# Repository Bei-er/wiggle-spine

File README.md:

This is the Wiggle **Spine**, an open hardware design for [Wiggleport](http://wiggleport.org)'s power and data hub.

* Each "spine" board has a 480 Mbit/s USB 2.0 uplink and 7 connectors for **modules**.
* Drive up to 14 speakers at 48/96 kHz per channel from one USB port.
* Connect sensors and lights, sync them perfectly with sound and each other.
* Use it to create objects and environments that are perfectly synchronized with immersive sound and vibration.
* Connect other audio-frequency devices like vibration transducers, LED strobes, and modular synthesizers.
* Use all the processing power in your PC, or run from an embedded Linux board like the Raspberry Pi 2.
* Gain accurate control of I/O timing from high-level languages like Javascript.

Scale it up or down
-------------------

* Multiple spines can be synchronized with cheap TOSLINK-style optical cables
  * USB links can go to the same or different computers, depending on how much processing power you need
  * Everyone shares a common audio clock and timestamps

* The spine also has a built-in DMX output so it's easy to add inexpensive lights and effects to your project
  * The output has galvanic isolation, to prevent grounding problems or audio hum
  * The DMX outputs can of course synchronize with all other inputs and outputs

* Wiggleport distributes power too, not just data
  * Flexible power input, 5 to 24 volts 
  * Lots of power, over 300 watts total
  * Each module has 5V, 3.3V, and 5-24V available
  * There's also a 5V power output for running a Raspberry Pi or other small computer
  * Also there's a watchdog timer, to reboot the computer if it stops running for any reason

Internals
---------

Wiggleport is an open source hardware design optimized for simple and straightforward real-time performance. It's based around an FTDI FT2232H high-speed USB FIFO interface, combined with a precision clock synthesizer and a tiny FPGA for glue logic. It stays simple and inexpensive by doing much of the work in software, relying on the powerful CPUs available on even small embedded Linux boards now.

Wiggleport isn't really a sound card, even though you can use it as one. It has its own APIs for C++, MIDI, and Javascript. You can write code for precisely timed multichannel sound installations on your laptop on Mac OS, for example, and run the same code on a Raspberry Pi later on.

Going even deeper, Wiggleport is really kind of a construction kit for hardware and drivers that stream signals in real-time. This reconfigurability is what lets Wiggleport automatically configure the various add-on modules, but you can also use this core directly to create your own hardware, with or without including an FPGA.

**Coming soon**... development is happening here now! You can follow the progress at [wiggleport.org](http://wiggleport.org).

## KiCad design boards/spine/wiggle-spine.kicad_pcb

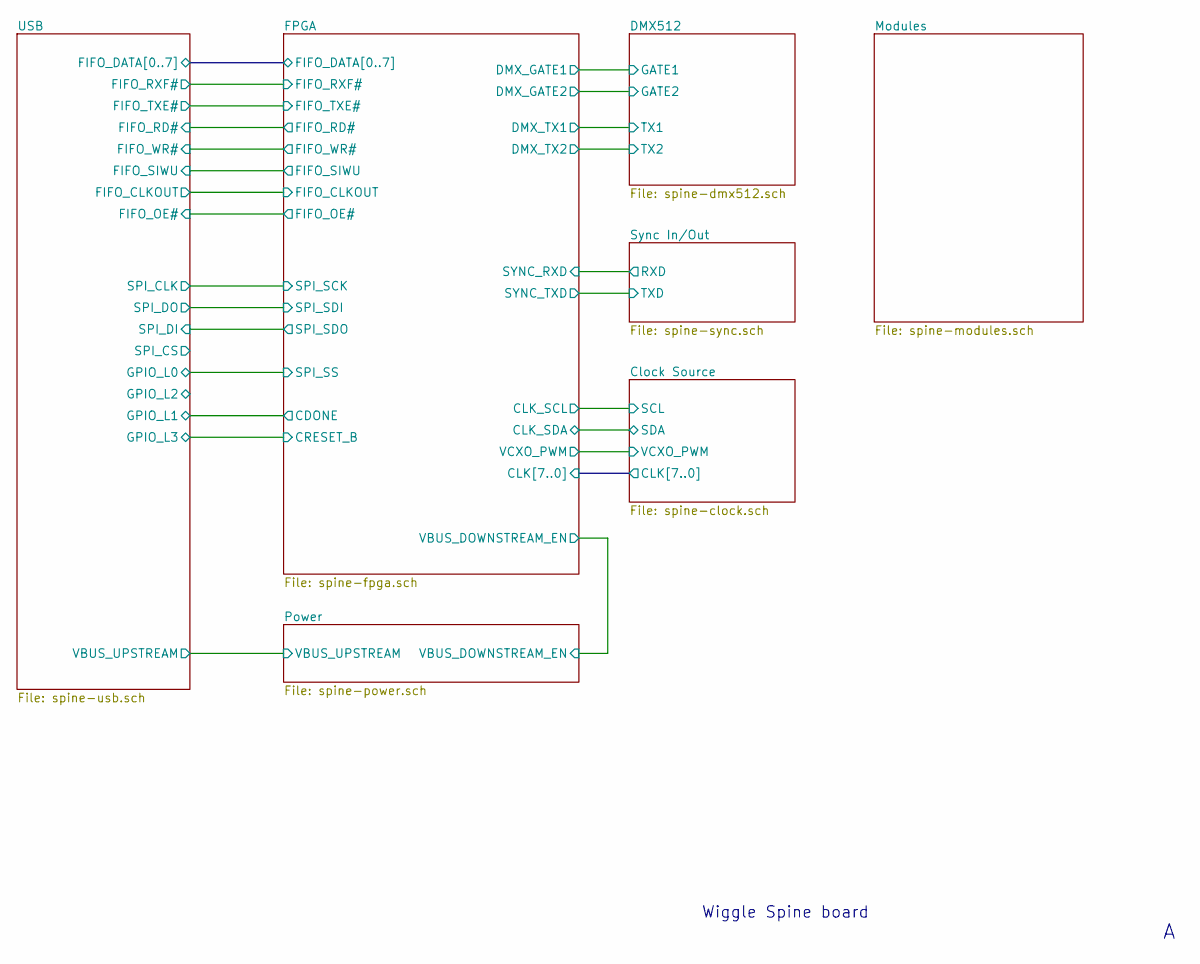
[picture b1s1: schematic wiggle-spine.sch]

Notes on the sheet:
Wiggle Spine board

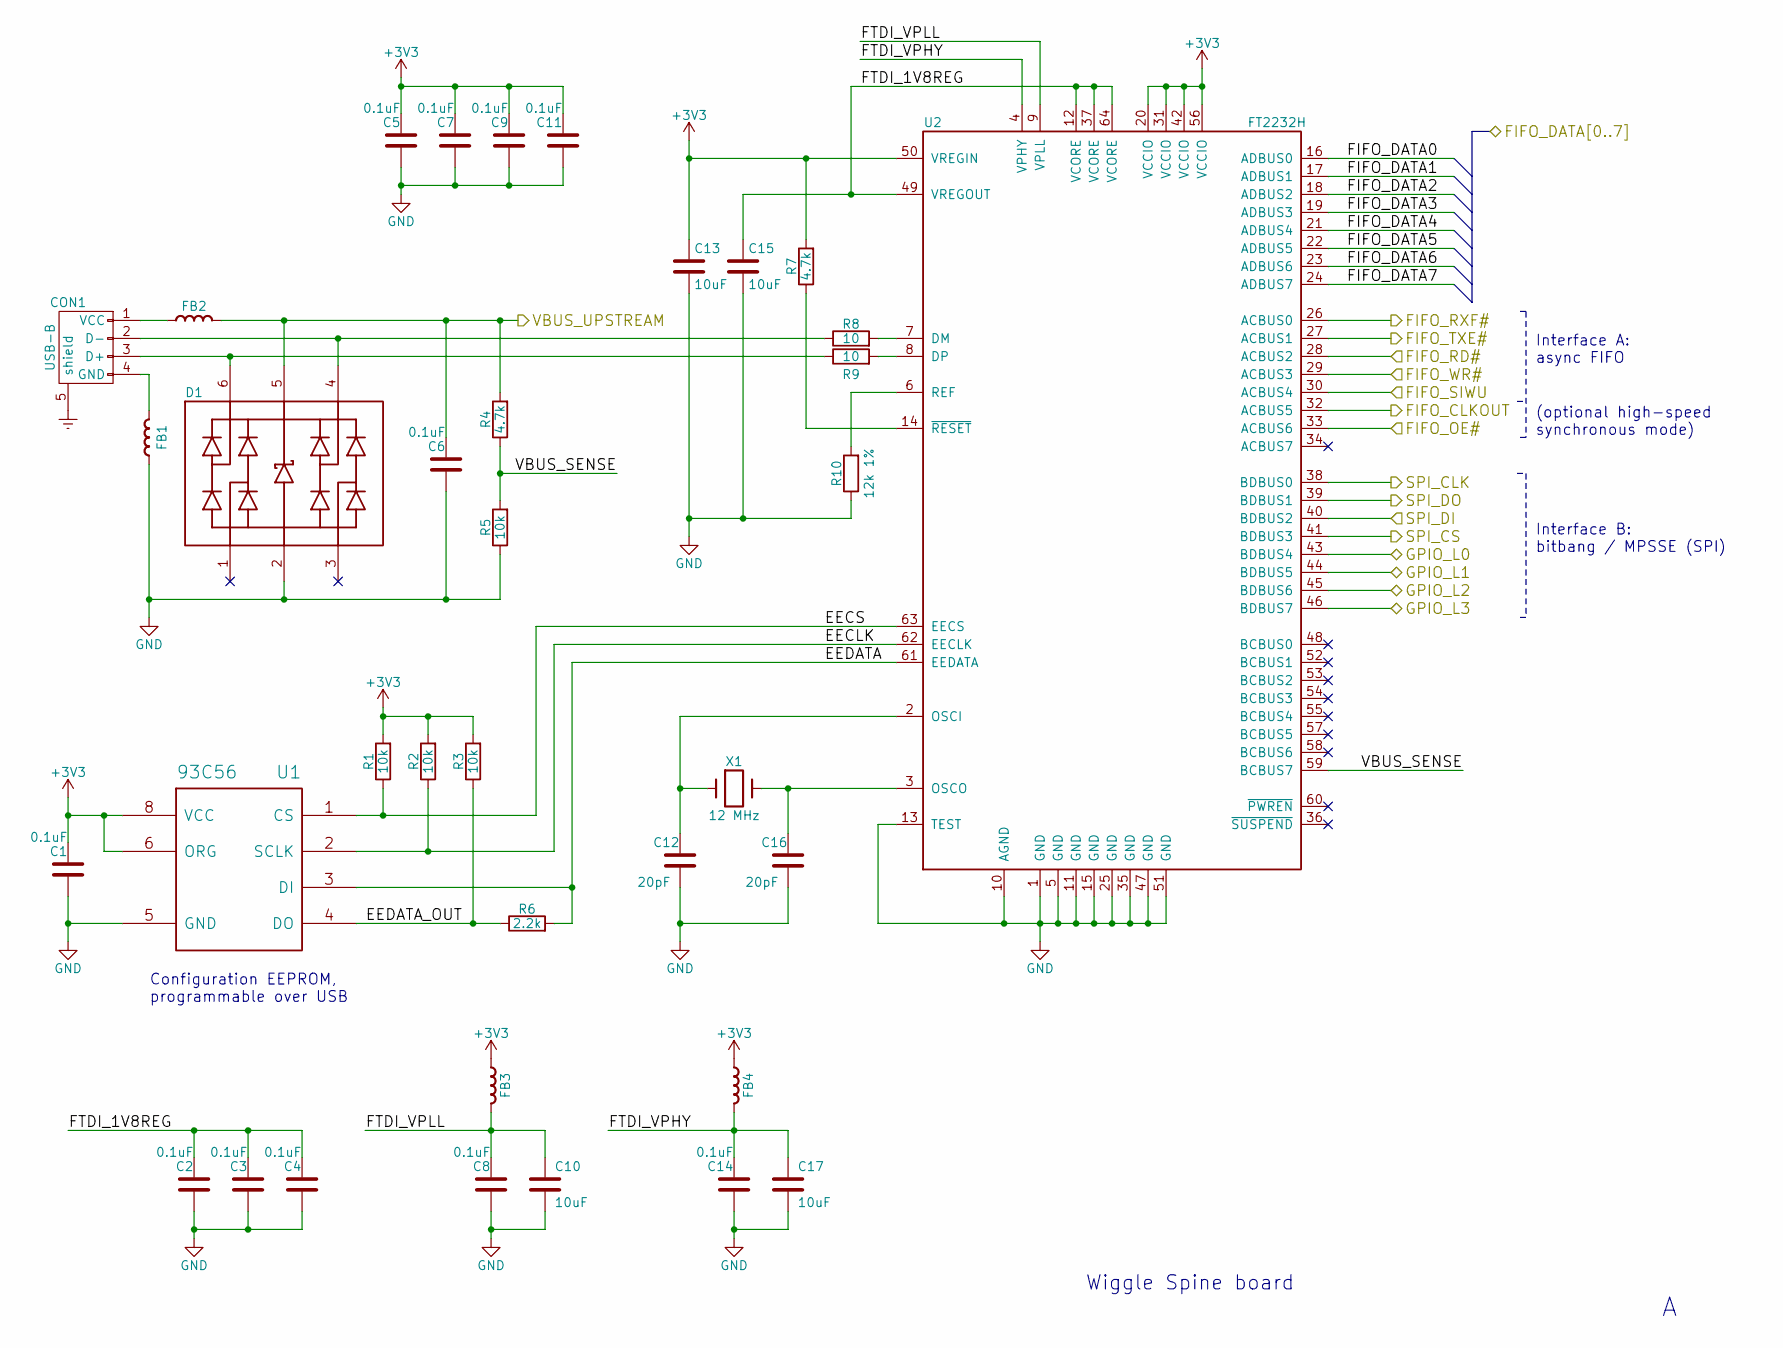
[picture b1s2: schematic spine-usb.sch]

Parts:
C1, C2, C3, C4, C5, C6, C7, C8, C9, C11, C14: 0.1uF; C_0805
C10, C13, C15, C17: 10uF; C_1206
C12, C16: 20pF; C_0805
CON1: USB-B; USB_B
D1: TVS DIODE 5.5VWM; SC-70-6
FB1, FB2, FB3, FB4: Ferrite bead; R_0805
R1, R2, R3, R5: 10k; R_0805
R4, R7: 4.7k; R_0805
R6: 2.2k; R_0805
R8, R9: 10; R_0805
R10: 12k 1%; R_0805
U1: 93C56; SOIC-8_3.9x4.9mm_Pitch1.27mm
U2: FT2232H; LQFP-64_10x10mm_Pitch0.5mm
X1: 12 MHz; Crystal_HC49-SD_SMD

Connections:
/FPGA/CDONE: U2.44 (BDBUS5); also elsewhere on the board
/FPGA/CRESET_B: U2.46 (BDBUS7); also elsewhere on the board
/FPGA/FIFO_CLKOUT: U2.32 (ACBUS5); also elsewhere on the board
/FPGA/FIFO_DATA0: U2.16 (ADBUS0); also elsewhere on the board
/FPGA/FIFO_DATA1: U2.17 (ADBUS1); also elsewhere on the board
/FPGA/FIFO_DATA2: U2.18 (ADBUS2); also elsewhere on the board
/FPGA/FIFO_DATA3: U2.19 (ADBUS3); also elsewhere on the board
/FPGA/FIFO_DATA4: U2.21 (ADBUS4); also elsewhere on the board
/FPGA/FIFO_DATA5: U2.22 (ADBUS5); also elsewhere on the board
/FPGA/FIFO_DATA6: U2.23 (ADBUS6); also elsewhere on the board
/FPGA/FIFO_DATA7: U2.24 (ADBUS7); also elsewhere on the board
/FPGA/FIFO_OE#: U2.33 (ACBUS6); also elsewhere on the board
/FPGA/FIFO_RD#: U2.28 (ACBUS2); also elsewhere on the board
/FPGA/FIFO_RXF#: U2.26 (ACBUS0); also elsewhere on the board
/FPGA/FIFO_SIWU: U2.30 (ACBUS4); also elsewhere on the board
/FPGA/FIFO_TXE#: U2.27 (ACBUS1); also elsewhere on the board
/FPGA/FIFO_WR#: U2.29 (ACBUS3); also elsewhere on the board
/Power/VBUS_UPSTREAM: C6.2, D1.5, FB2.2, R4.2; also elsewhere on the board
/USB/EECLK: R2.1, U1.2 (SCLK), U2.62 (EECLK)
/USB/EECS: R1.1, U1.1 (CS), U2.63 (EECS)
/USB/EEDATA: R6.2, U1.3 (DI), U2.61 (EEDATA)
/USB/EEDATA_OUT: R3.1, R6.1, U1.4 (DO)
/USB/FTDI_1V8REG: C2.2, C3.2, C4.2, C15.1, U2.12 (VCORE), U2.37 (VCORE), U2.49 (VREGOUT), U2.64 (VCORE)
/USB/FTDI_VPHY: C14.2, C17.1, FB4.2, U2.4 (VPHY)
/USB/FTDI_VPLL: C8.2, C10.1, FB3.2, U2.9 (VPLL)
/USB/GPIO_L0: U2.43 (BDBUS4); also elsewhere on the board
/USB/SPI_CLK: U2.38 (BDBUS0); also elsewhere on the board
/USB/SPI_DI: U2.40 (BDBUS2); also elsewhere on the board
/USB/SPI_DO: U2.39 (BDBUS1); also elsewhere on the board
/USB/VBUS_SENSE: R4.1, R5.2, U2.59 (BCBUS7)
Earth: CON1.5 (shield); also elsewhere on the board
GND: C1.1, C2.1, C3.1, C4.1, C5.1, C6.1, C7.1, C8.1, C9.1, C10.2, C11.1, C12.1, C13.2, C14.1, C15.2, C16.1, C17.2, D1.2, FB1.1, R5.1, R10.1, U1.5 (GND), U2.1 (GND), U2.5 (GND), U2.10 (AGND), U2.11 (GND), U2.13 (TEST), U2.15 (GND), U2.25 (GND), U2.35 (GND), U2.47 (GND), U2.51 (GND); also elsewhere on the board
unnamed: C12.2, U2.2 (OSCI), X1.1
unnamed: C16.2, U2.3 (OSCO), X1.2
unnamed: CON1.1 (VCC), FB2.1
unnamed: CON1.2 (D-), D1.4, R8.1
unnamed: CON1.3 (D+), D1.6, R9.1
unnamed: CON1.4 (GND), FB1.2
unnamed: R7.1, U2.14 (~RESET)
unnamed: R8.2, U2.7 (DM)
unnamed: R9.2, U2.8 (DP)
unnamed: R10.2, U2.6 (REF)

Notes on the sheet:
(optional high-speed synchronous mode)
Interface A: async FIFO
Interface B: bitbang / MPSSE (SPI)
Configuration EEPROM, programmable over USB
Wiggle Spine board

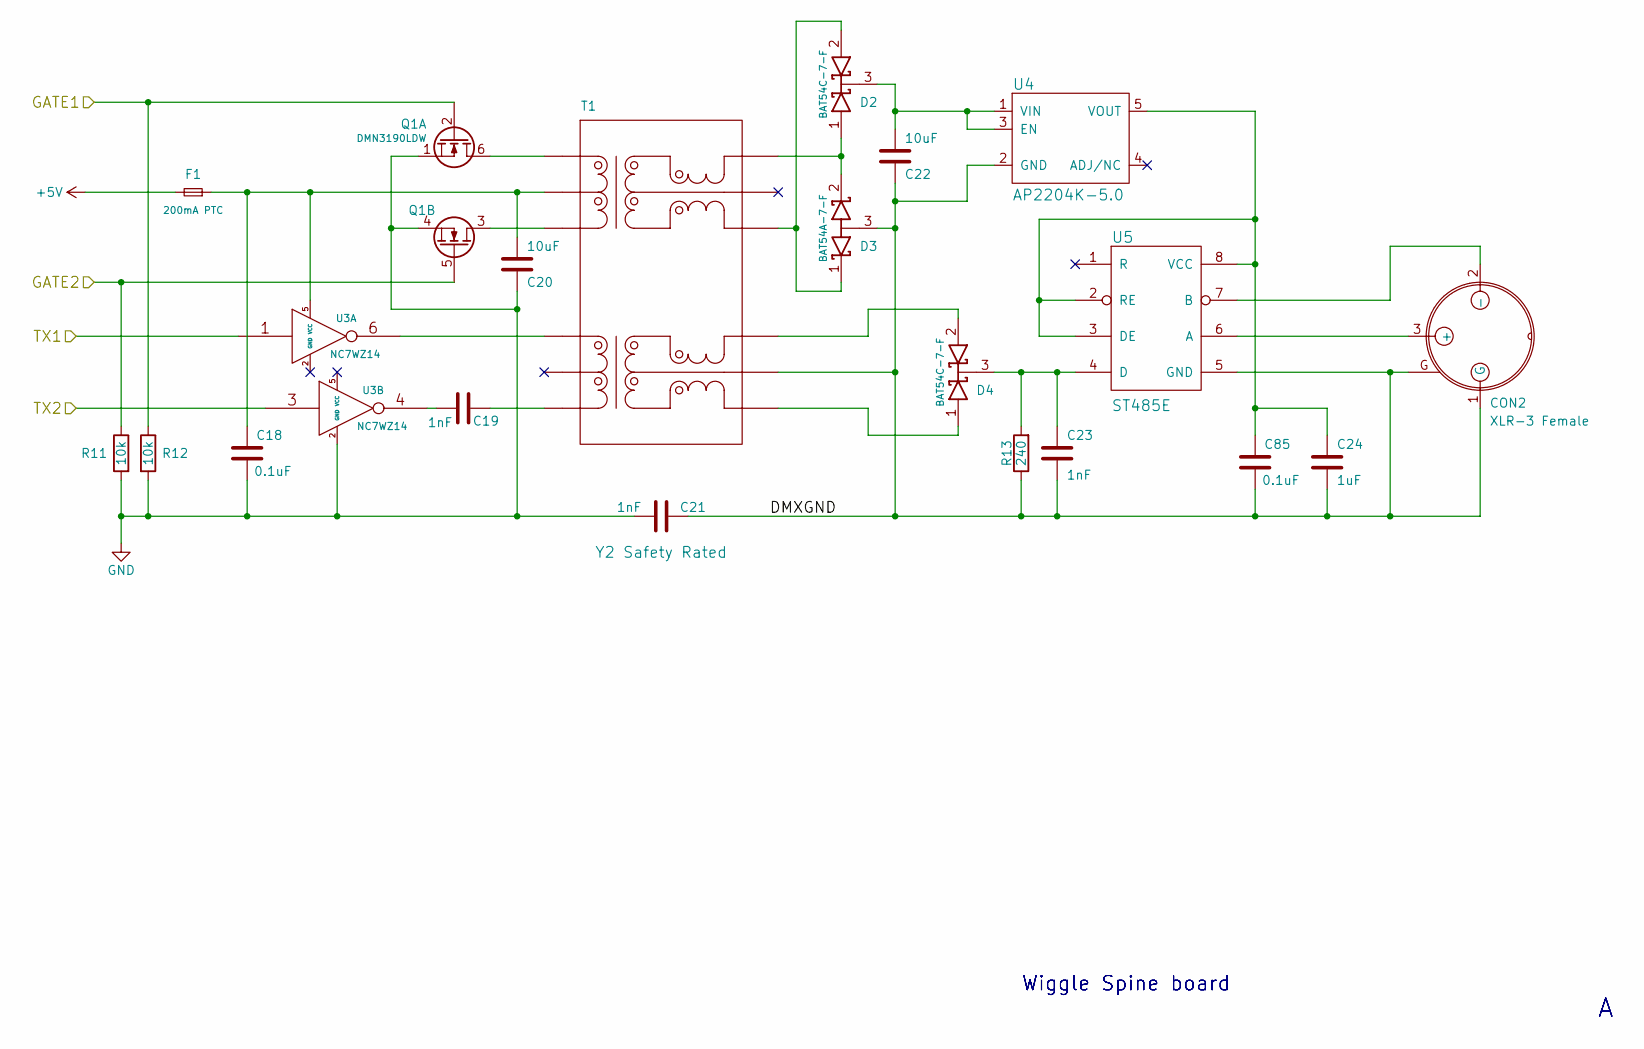
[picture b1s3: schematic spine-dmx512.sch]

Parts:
C18, C85: 0.1uF; C_0805
C19, C23: 1nF; C_0805
C20, C22: 10uF; C_1206
C21: 1nF; C_1808; Safety Rating Y2 Safety Rated
C24: 1uF; C_0805
CON2: XLR-3 Female; XLR3MC
D2, D4: BAT54 2x common cathode; SOT-23
D3: BAT54 2x common anode; SOT-23
F1: 200mA PTC; R_1206
Q1: DMN3190LDW; SC-70-6
R11, R12: 10k; R_0805
R13: 240; R_0805
T1: 10/100baseT transformer; SOIC-16_7.5x10.3mm_Pitch1.27mm
U3: NC7WZ14; SC-70-6
U4: AP2204K-5.0; SOT-23-5
U5: ST485E; SOIC-8_3.9x4.9mm_Pitch1.27mm

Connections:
+5V: F1.2; also elsewhere on the board
/DMX512/DMXGND: C21.1, C22.2, C23.2, C24.2, C85.1, CON2.1 (G), CON2.G, D3.3 (A), R13.1, T1.7, U4.2 (GND), U5.5 (GND)
/FPGA/DMX_GATE1: Q1.2 (G), R12.1; also elsewhere on the board
/FPGA/DMX_GATE2: Q1.5 (G), R11.1; also elsewhere on the board
/FPGA/DMX_TX1: U3.1; also elsewhere on the board
/FPGA/DMX_TX2: U3.3; also elsewhere on the board
GND: C18.1, C20.2, C21.2, Q1.1 (S), Q1.4 (S), R11.2, R12.2, U3.2 (GND); also elsewhere on the board
unnamed: C18.2, C20.1, F1.1, T1.15, U3.5 (VCC)
unnamed: C19.1, T1.9
unnamed: C19.2, U3.4
unnamed: C22.1, D2.3 (K), U4.1 (VIN), U4.3 (EN)
unnamed: C23.1, D4.3 (K), R13.2, U5.4 (D)
unnamed: C24.1, C85.2, U4.5 (VOUT), U5.2 (RE), U5.3 (DE), U5.8 (VCC)
unnamed: CON2.2 (-), U5.7 (B)
unnamed: CON2.3 (+), U5.6 (A)
unnamed: D2.1 (A), D3.2 (K), T1.1
unnamed: D2.2 (A), D3.1 (K), T1.3
unnamed: D4.1 (A), T1.8
unnamed: D4.2 (A), T1.6
unnamed: Q1.3 (D), T1.14
unnamed: Q1.6 (D), T1.16
unnamed: T1.11, U3.6

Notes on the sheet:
Wiggle Spine board

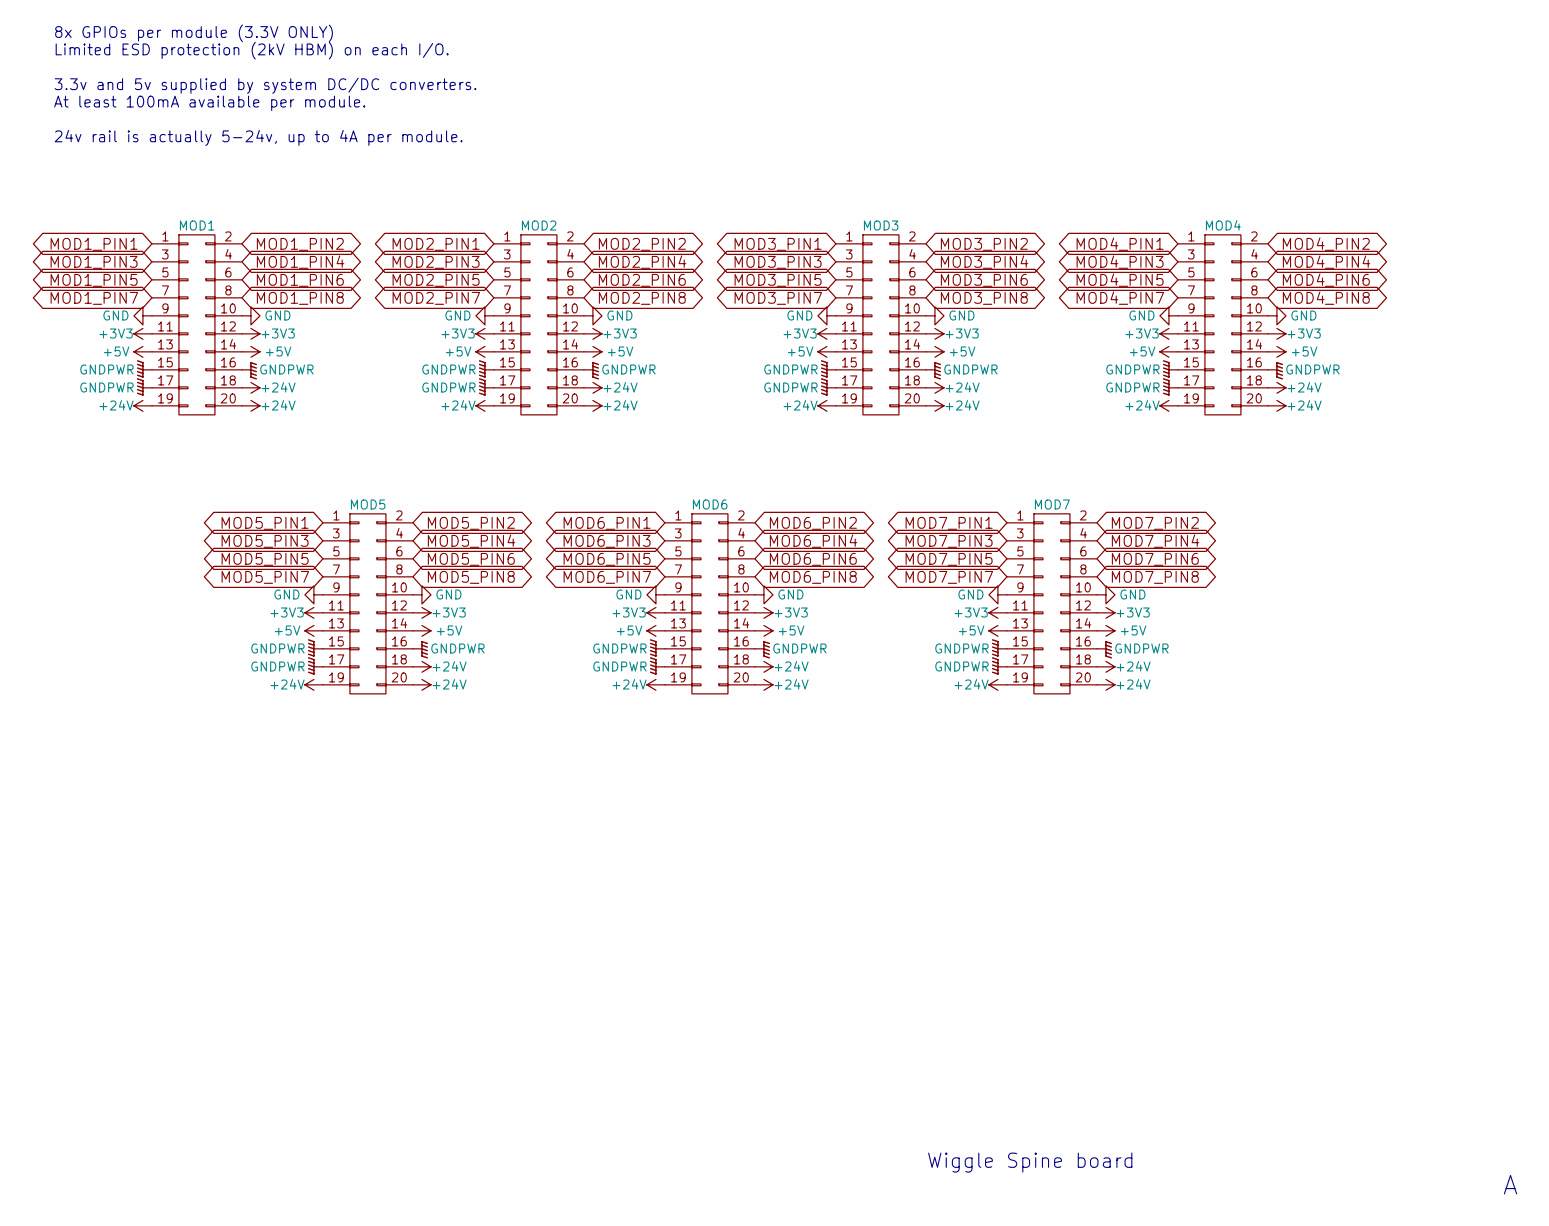
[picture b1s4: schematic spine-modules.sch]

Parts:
MOD1, MOD2, MOD3, MOD4, MOD5, MOD6, MOD7: 2.54mm 2x10 right angle female header; Socket_Strip_Angled_2x10_Mirror

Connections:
+5V: MOD1.13, MOD1.14, MOD2.13, MOD2.14, MOD3.13, MOD3.14, MOD4.13, MOD4.14, MOD5.13, MOD5.14, MOD6.13, MOD6.14, MOD7.13, MOD7.14; also elsewhere on the board
+24V: MOD1.18, MOD1.19, MOD1.20, MOD2.18, MOD2.19, MOD2.20, MOD3.18, MOD3.19, MOD3.20, MOD4.18, MOD4.19, MOD4.20, MOD5.18, MOD5.19, MOD5.20, MOD6.18, MOD6.19, MOD6.20, MOD7.18, MOD7.19, MOD7.20; also elsewhere on the board
GND: MOD1.9, MOD1.10, MOD2.9, MOD2.10, MOD3.9, MOD3.10, MOD4.9, MOD4.10, MOD5.9, MOD5.10, MOD6.9, MOD6.10, MOD7.9, MOD7.10; also elsewhere on the board
GNDPWR: MOD1.15, MOD1.16, MOD1.17, MOD2.15, MOD2.16, MOD2.17, MOD3.15, MOD3.16, MOD3.17, MOD4.15, MOD4.16, MOD4.17, MOD5.15, MOD5.16, MOD5.17, MOD6.15, MOD6.16, MOD6.17, MOD7.15, MOD7.16, MOD7.17; also elsewhere on the board
MOD1_PIN1: MOD1.1; also elsewhere on the board
MOD1_PIN2: MOD1.2; also elsewhere on the board
MOD1_PIN3: MOD1.3; also elsewhere on the board
MOD1_PIN4: MOD1.4; also elsewhere on the board
MOD1_PIN5: MOD1.5; also elsewhere on the board
MOD1_PIN6: MOD1.6; also elsewhere on the board
MOD1_PIN7: MOD1.7; also elsewhere on the board
MOD1_PIN8: MOD1.8; also elsewhere on the board
MOD2_PIN1: MOD2.1; also elsewhere on the board
MOD2_PIN2: MOD2.2; also elsewhere on the board
MOD2_PIN3: MOD2.3; also elsewhere on the board
MOD2_PIN4: MOD2.4; also elsewhere on the board
MOD2_PIN5: MOD2.5; also elsewhere on the board
MOD2_PIN6: MOD2.6; also elsewhere on the board
MOD2_PIN7: MOD2.7; also elsewhere on the board
MOD2_PIN8: MOD2.8; also elsewhere on the board
MOD3_PIN1: MOD3.1; also elsewhere on the board
MOD3_PIN2: MOD3.2; also elsewhere on the board
MOD3_PIN3: MOD3.3; also elsewhere on the board
MOD3_PIN4: MOD3.4; also elsewhere on the board
MOD3_PIN5: MOD3.5; also elsewhere on the board
MOD3_PIN6: MOD3.6; also elsewhere on the board
MOD3_PIN7: MOD3.7; also elsewhere on the board
MOD3_PIN8: MOD3.8; also elsewhere on the board
MOD4_PIN1: MOD4.1; also elsewhere on the board
MOD4_PIN2: MOD4.2; also elsewhere on the board
MOD4_PIN3: MOD4.3; also elsewhere on the board
MOD4_PIN4: MOD4.4; also elsewhere on the board
MOD4_PIN5: MOD4.5; also elsewhere on the board
MOD4_PIN6: MOD4.6; also elsewhere on the board
MOD4_PIN7: MOD4.7; also elsewhere on the board
MOD4_PIN8: MOD4.8; also elsewhere on the board
MOD5_PIN1: MOD5.1; also elsewhere on the board
MOD5_PIN2: MOD5.2; also elsewhere on the board
MOD5_PIN3: MOD5.3; also elsewhere on the board
MOD5_PIN4: MOD5.4; also elsewhere on the board
MOD5_PIN5: MOD5.5; also elsewhere on the board
MOD5_PIN6: MOD5.6; also elsewhere on the board
MOD5_PIN7: MOD5.7; also elsewhere on the board
MOD5_PIN8: MOD5.8; also elsewhere on the board
MOD6_PIN1: MOD6.1; also elsewhere on the board
MOD6_PIN2: MOD6.2; also elsewhere on the board
MOD6_PIN3: MOD6.3; also elsewhere on the board
MOD6_PIN4: MOD6.4; also elsewhere on the board
MOD6_PIN5: MOD6.5; also elsewhere on the board
MOD6_PIN6: MOD6.6; also elsewhere on the board
MOD6_PIN7: MOD6.7; also elsewhere on the board
MOD6_PIN8: MOD6.8; also elsewhere on the board
MOD7_PIN1: MOD7.1; also elsewhere on the board
MOD7_PIN2: MOD7.2; also elsewhere on the board
MOD7_PIN3: MOD7.3; also elsewhere on the board
MOD7_PIN4: MOD7.4; also elsewhere on the board
MOD7_PIN5: MOD7.5; also elsewhere on the board
MOD7_PIN6: MOD7.6; also elsewhere on the board
MOD7_PIN7: MOD7.7; also elsewhere on the board
MOD7_PIN8: MOD7.8; also elsewhere on the board

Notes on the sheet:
8x GPIOs per module (3.3V ONLY) Limited ESD protection (2kV HBM) on each I/O. 3.3v and 5v supplied by system DC/DC converters. At least 100mA available per module. 24v rail is actually 5-24v, up to 4A per module.
Wiggle Spine board

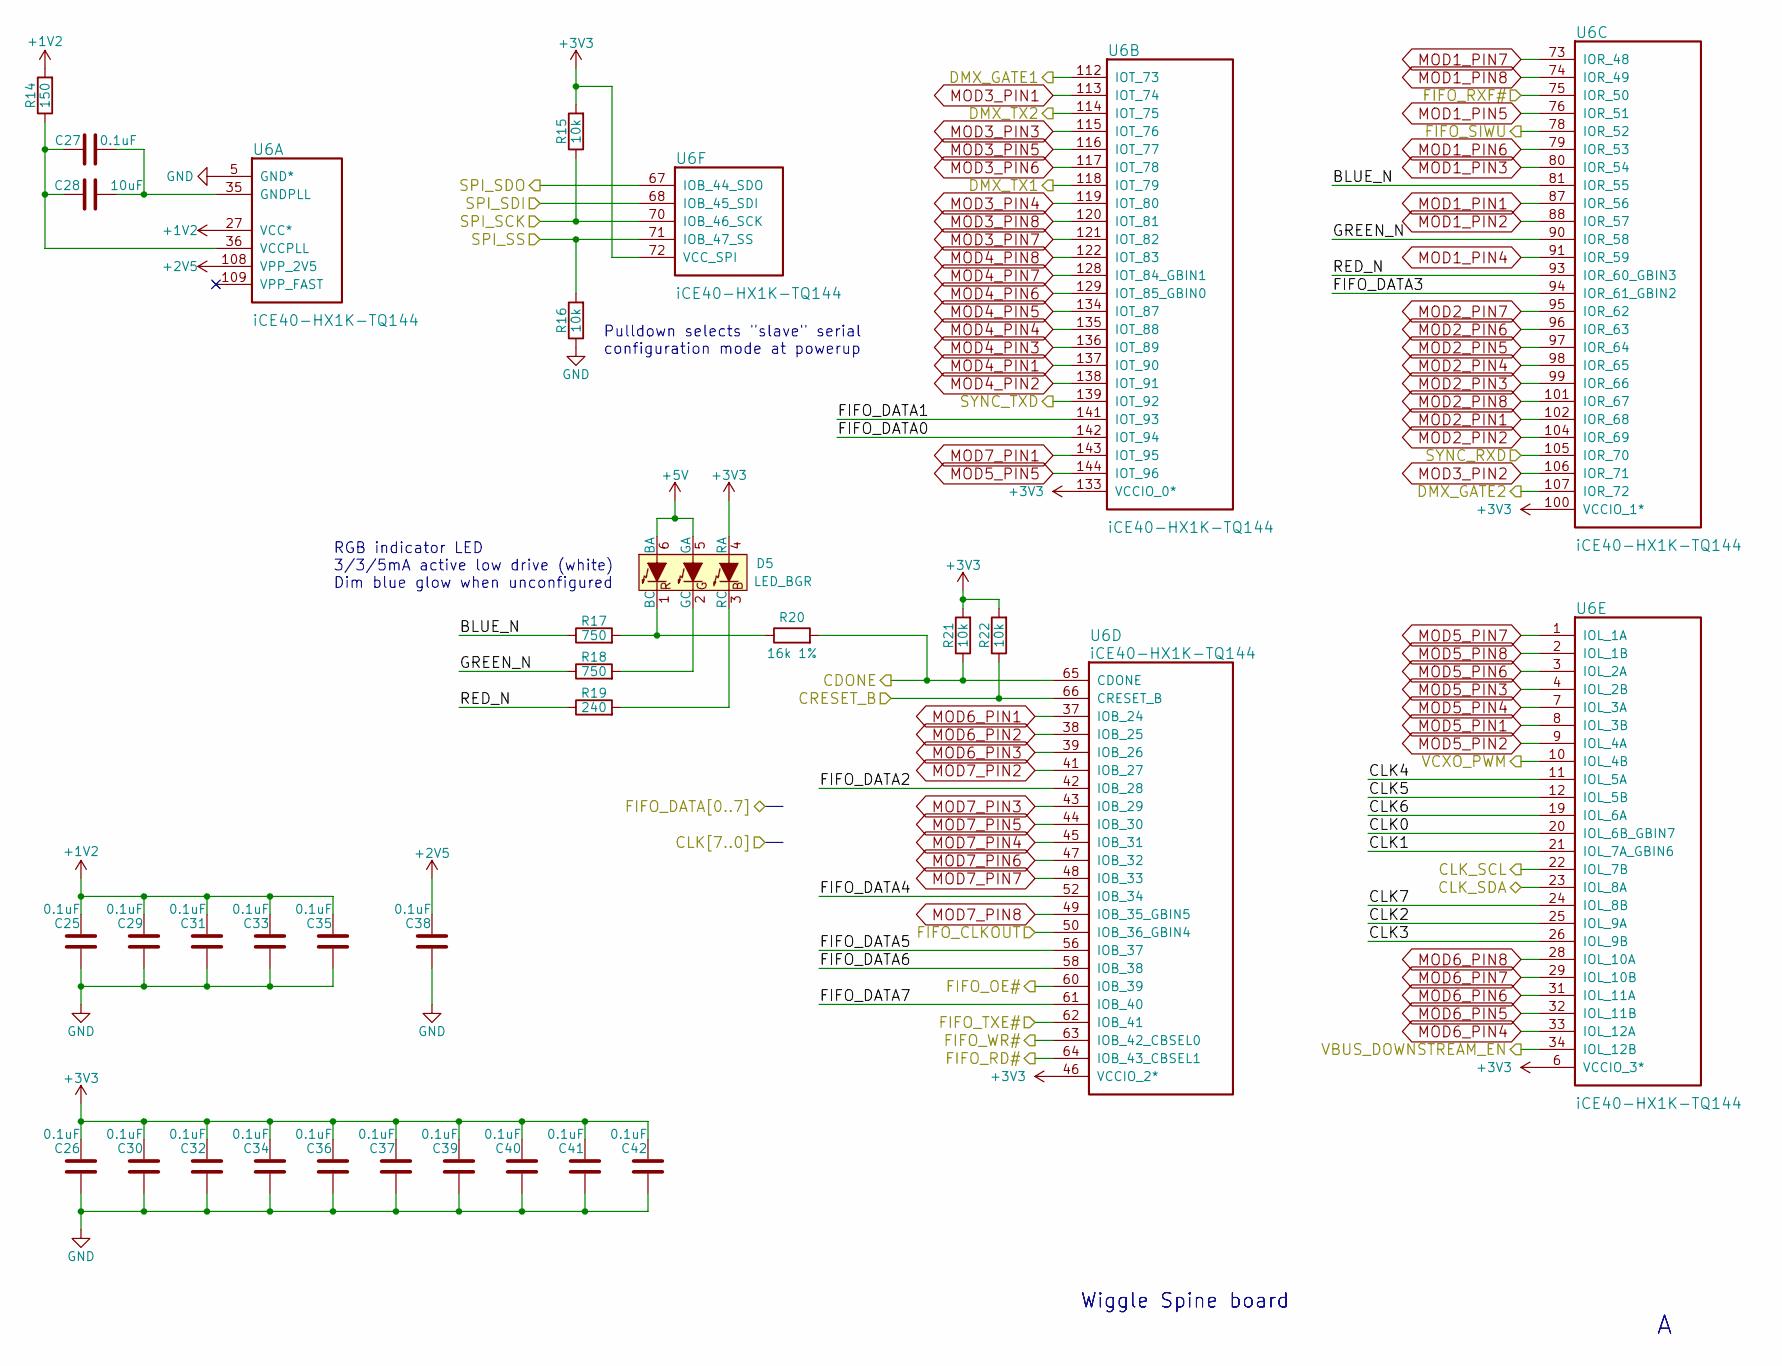
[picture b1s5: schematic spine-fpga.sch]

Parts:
C25, C26, C27, C29, C30, C31, C32, C33, C34, C35, C36, C37, C38, C39, C40, C41, C42: 0.1uF; C_0805
C28: 10uF; C_1206
D5: LED_BGR; LED_RGB_PLLC-6
R14: 150; R_0805
R15, R16, R21, R22: 10k; R_0805
R17, R18: 750; R_0805
R19: 240; R_0805
R20: 16k 1%; R_0805
U6: iCE40-HX1K-TQ144; TQFP-144_20x20mm_Pitch0.5mm

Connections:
+1V2: C25.2, C29.2, C31.2, C33.2, C35.2, R14.2, U6.27 (VCC*), U6.51 (VCC*), U6.92 (VCC*), U6.111 (VCC*); also elsewhere on the board
+2V5: C38.2, U6.108 (VPP_2V5); also elsewhere on the board
+5V: D5.5 (GA), D5.6 (BA); also elsewhere on the board
/Clock Source/CLK0: U6.20 (IOL_6B_GBIN7); also elsewhere on the board
/Clock Source/CLK1: U6.21 (IOL_7A_GBIN6); also elsewhere on the board
/Clock Source/CLK2: U6.25 (IOL_9A); also elsewhere on the board
/Clock Source/CLK3: U6.26 (IOL_9B); also elsewhere on the board
/Clock Source/CLK4: U6.11 (IOL_5A); also elsewhere on the board
/Clock Source/CLK5: U6.12 (IOL_5B); also elsewhere on the board
/Clock Source/CLK6: U6.19 (IOL_6A); also elsewhere on the board
/Clock Source/CLK7: U6.24 (IOL_8B); also elsewhere on the board
/Clock Source/VCXO_PWM: U6.10 (IOL_4B); also elsewhere on the board
/FPGA/BLUE_N: R17.1, U6.81 (IOR_55)
/FPGA/CDONE: R20.2, R21.1, U6.65 (CDONE); also elsewhere on the board
/FPGA/CLK_SCL: U6.22 (IOL_7B); also elsewhere on the board
/FPGA/CLK_SDA: U6.23 (IOL_8A); also elsewhere on the board
/FPGA/CRESET_B: R22.1, U6.66 (CRESET_B); also elsewhere on the board
/FPGA/DMX_GATE1: U6.112 (IOT_73); also elsewhere on the board
/FPGA/DMX_GATE2: U6.107 (IOR_72); also elsewhere on the board
/FPGA/DMX_TX1: U6.118 (IOT_79); also elsewhere on the board
/FPGA/DMX_TX2: U6.114 (IOT_75); also elsewhere on the board
/FPGA/FIFO_CLKOUT: U6.50 (IOB_36_GBIN4); also elsewhere on the board
/FPGA/FIFO_DATA0: U6.142 (IOT_94); also elsewhere on the board
/FPGA/FIFO_DATA1: U6.141 (IOT_93); also elsewhere on the board
/FPGA/FIFO_DATA2: U6.42 (IOB_28); also elsewhere on the board
/FPGA/FIFO_DATA3: U6.94 (IOR_61_GBIN2); also elsewhere on the board
/FPGA/FIFO_DATA4: U6.52 (IOB_34); also elsewhere on the board
/FPGA/FIFO_DATA5: U6.56 (IOB_37); also elsewhere on the board
/FPGA/FIFO_DATA6: U6.58 (IOB_38); also elsewhere on the board
/FPGA/FIFO_DATA7: U6.61 (IOB_40); also elsewhere on the board
/FPGA/FIFO_OE#: U6.60 (IOB_39); also elsewhere on the board
/FPGA/FIFO_RD#: U6.64 (IOB_43_CBSEL1); also elsewhere on the board
/FPGA/FIFO_RXF#: U6.75 (IOR_50); also elsewhere on the board
/FPGA/FIFO_SIWU: U6.78 (IOR_52); also elsewhere on the board
/FPGA/FIFO_TXE#: U6.62 (IOB_41); also elsewhere on the board
/FPGA/FIFO_WR#: U6.63 (IOB_42_CBSEL0); also elsewhere on the board
/FPGA/GREEN_N: R18.1, U6.90 (IOR_58)
/FPGA/RED_N: R19.1, U6.93 (IOR_60_GBIN3)
/FPGA/SYNC_TXD: U6.139 (IOT_92); also elsewhere on the board
/FPGA/VBUS_DOWNSTREAM_EN: U6.34 (IOL_12B); also elsewhere on the board
/Sync In/Out/RXD: U6.105 (IOR_70); also elsewhere on the board
/USB/GPIO_L0: R16.2, U6.71 (IOB_47_SS); also elsewhere on the board
/USB/SPI_CLK: R15.1, U6.70 (IOB_46_SCK); also elsewhere on the board
/USB/SPI_DI: U6.67 (IOB_44_SDO); also elsewhere on the board
/USB/SPI_DO: U6.68 (IOB_45_SDI); also elsewhere on the board
GND: C25.1, C26.1, C29.1, C30.1, C31.1, C32.1, C33.1, C34.1, C35.1, C36.1, C37.1, C38.1, C39.1, C40.1, C41.1, C42.1, R16.1, U6.5 (GND*), U6.13 (GND*), U6.14 (GND*), U6.59 (GND*), U6.69 (GND*), U6.86 (GND*), U6.103 (GND*), U6.132 (GND*), U6.140 (GND*); also elsewhere on the board
MOD1_PIN1: U6.87 (IOR_56); also elsewhere on the board
MOD1_PIN2: U6.88 (IOR_57); also elsewhere on the board
MOD1_PIN3: U6.80 (IOR_54); also elsewhere on the board
MOD1_PIN4: U6.91 (IOR_59); also elsewhere on the board
MOD1_PIN5: U6.76 (IOR_51); also elsewhere on the board
MOD1_PIN6: U6.79 (IOR_53); also elsewhere on the board
MOD1_PIN7: U6.73 (IOR_48); also elsewhere on the board
MOD1_PIN8: U6.74 (IOR_49); also elsewhere on the board
MOD2_PIN1: U6.102 (IOR_68); also elsewhere on the board
MOD2_PIN2: U6.104 (IOR_69); also elsewhere on the board
MOD2_PIN3: U6.99 (IOR_66); also elsewhere on the board
MOD2_PIN4: U6.98 (IOR_65); also elsewhere on the board
MOD2_PIN5: U6.97 (IOR_64); also elsewhere on the board
MOD2_PIN6: U6.96 (IOR_63); also elsewhere on the board
MOD2_PIN7: U6.95 (IOR_62); also elsewhere on the board
MOD2_PIN8: U6.101 (IOR_67); also elsewhere on the board
MOD3_PIN1: U6.113 (IOT_74); also elsewhere on the board
MOD3_PIN2: U6.106 (IOR_71); also elsewhere on the board
MOD3_PIN3: U6.115 (IOT_76); also elsewhere on the board
MOD3_PIN4: U6.119 (IOT_80); also elsewhere on the board
MOD3_PIN5: U6.116 (IOT_77); also elsewhere on the board
MOD3_PIN6: U6.117 (IOT_78); also elsewhere on the board
MOD3_PIN7: U6.121 (IOT_82); also elsewhere on the board
MOD3_PIN8: U6.120 (IOT_81); also elsewhere on the board
MOD4_PIN1: U6.137 (IOT_90); also elsewhere on the board
MOD4_PIN2: U6.138 (IOT_91); also elsewhere on the board
MOD4_PIN3: U6.136 (IOT_89); also elsewhere on the board
MOD4_PIN4: U6.135 (IOT_88); also elsewhere on the board
MOD4_PIN5: U6.134 (IOT_87); also elsewhere on the board
MOD4_PIN6: U6.129 (IOT_85_GBIN0); also elsewhere on the board
MOD4_PIN7: U6.128 (IOT_84_GBIN1); also elsewhere on the board
MOD4_PIN8: U6.122 (IOT_83); also elsewhere on the board
MOD5_PIN1: U6.8 (IOL_3B); also elsewhere on the board
MOD5_PIN2: U6.9 (IOL_4A); also elsewhere on the board
MOD5_PIN3: U6.4 (IOL_2B); also elsewhere on the board
MOD5_PIN4: U6.7 (IOL_3A); also elsewhere on the board
MOD5_PIN5: U6.144 (IOT_96); also elsewhere on the board
MOD5_PIN6: U6.3 (IOL_2A); also elsewhere on the board
MOD5_PIN7: U6.1 (IOL_1A); also elsewhere on the board
MOD5_PIN8: U6.2 (IOL_1B); also elsewhere on the board
MOD6_PIN1: U6.37 (IOB_24); also elsewhere on the board
MOD6_PIN2: U6.38 (IOB_25); also elsewhere on the board
MOD6_PIN3: U6.39 (IOB_26); also elsewhere on the board
MOD6_PIN4: U6.33 (IOL_12A); also elsewhere on the board
MOD6_PIN5: U6.32 (IOL_11B); also elsewhere on the board
MOD6_PIN6: U6.31 (IOL_11A); also elsewhere on the board
MOD6_PIN7: U6.29 (IOL_10B); also elsewhere on the board
MOD6_PIN8: U6.28 (IOL_10A); also elsewhere on the board
MOD7_PIN1: U6.143 (IOT_95); also elsewhere on the board
MOD7_PIN2: U6.41 (IOB_27); also elsewhere on the board
MOD7_PIN3: U6.43 (IOB_29); also elsewhere on the board
MOD7_PIN4: U6.45 (IOB_31); also elsewhere on the board
MOD7_PIN5: U6.44 (IOB_30); also elsewhere on the board
MOD7_PIN6: U6.47 (IOB_32); also elsewhere on the board
MOD7_PIN7: U6.48 (IOB_33); also elsewhere on the board
MOD7_PIN8: U6.49 (IOB_35_GBIN5); also elsewhere on the board
unnamed: C27.1, C28.2, U6.35 (GNDPLL)
unnamed: C27.2, C28.1, R14.1, U6.36 (VCCPLL)
unnamed: D5.1 (BC), R17.2, R20.1
unnamed: D5.2 (GC), R18.2
unnamed: D5.3 (RC), R19.2

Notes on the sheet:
Pulldown selects "slave" serial configuration mode at powerup
RGB indicator LED 3/3/5mA active low drive (white) Dim blue glow when unconfigured
Wiggle Spine board

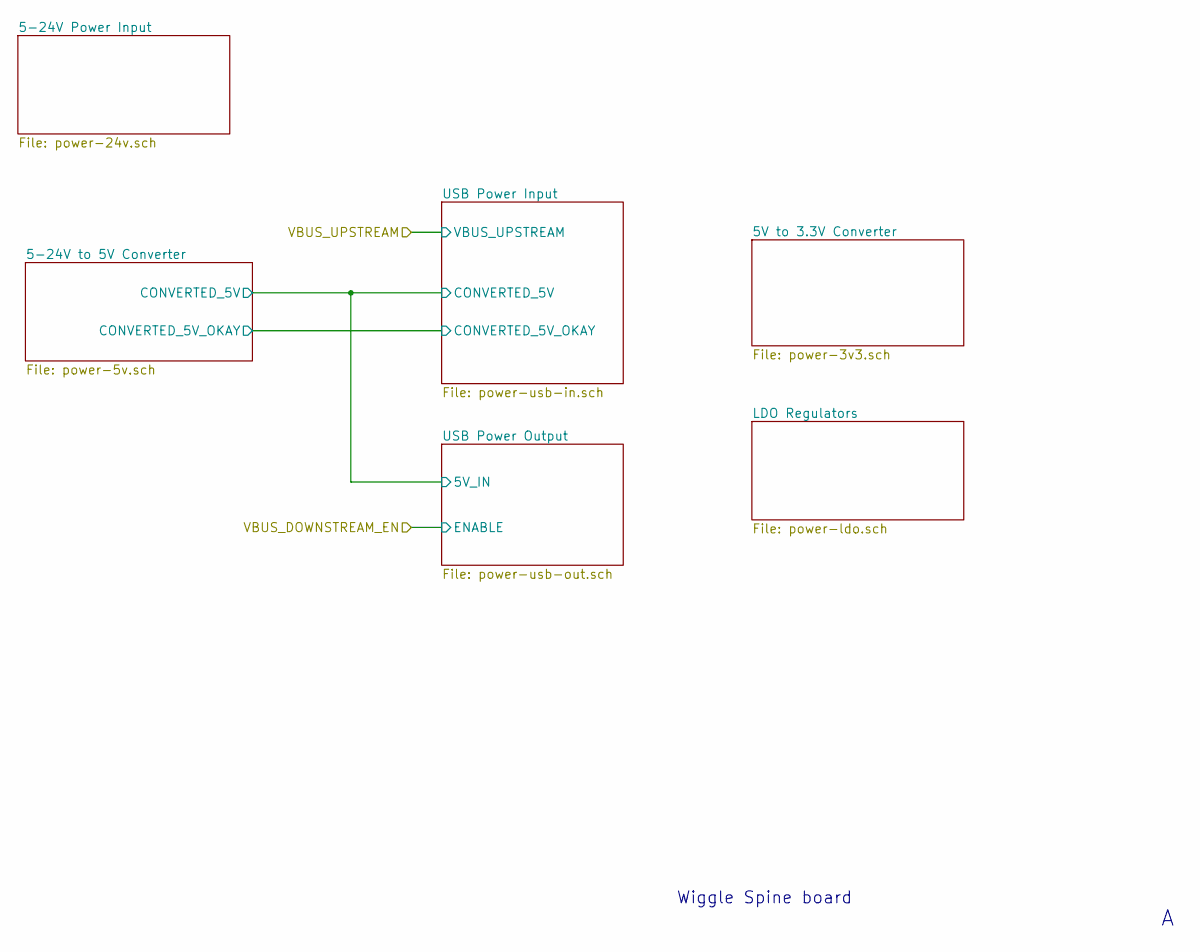
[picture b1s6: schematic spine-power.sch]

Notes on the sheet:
Wiggle Spine board
